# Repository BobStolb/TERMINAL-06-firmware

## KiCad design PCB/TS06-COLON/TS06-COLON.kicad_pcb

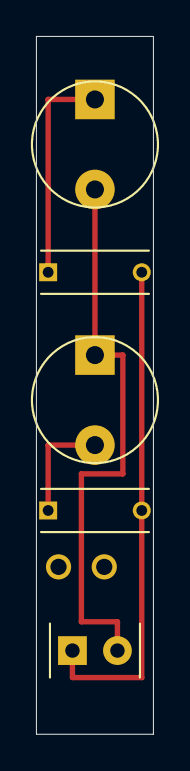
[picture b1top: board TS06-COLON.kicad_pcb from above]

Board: 2 copper layers, 6.5 x 38.8 mm, 5 parts (0 on the bottom side), 4 nets.

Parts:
R1, R2: 220k; TS06_R_Axial_EdgeToEdge
V1, V2: INS1; TS06_INS1_Lamp
XS4: XS4; TS06_XS4_JST_XH_2p_RA

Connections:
COLON_RET: V1.2, V2.1, XS4.2
HV185: R1.2, R2.2, XS4.1
R1_LINK: R1.1, V1.1
R2_LINK: R2.1, V2.2

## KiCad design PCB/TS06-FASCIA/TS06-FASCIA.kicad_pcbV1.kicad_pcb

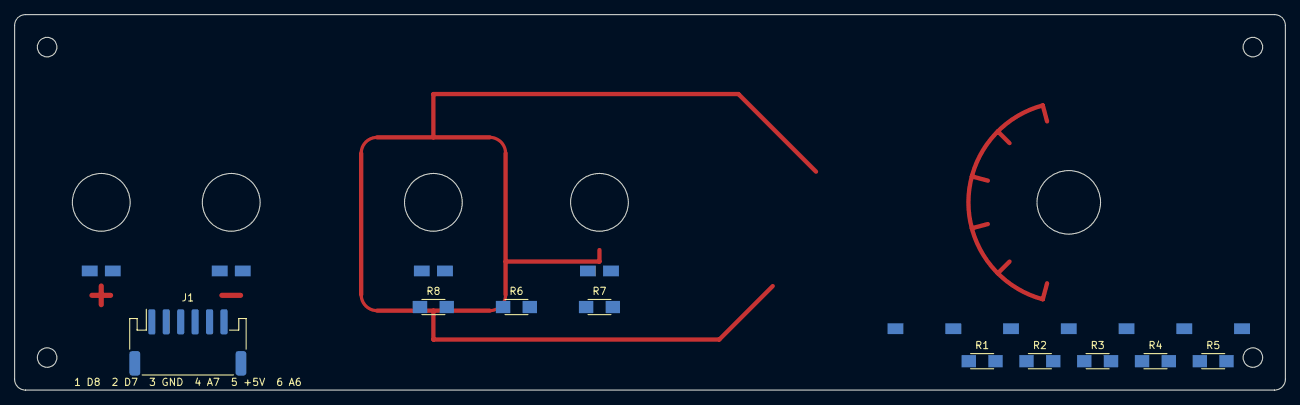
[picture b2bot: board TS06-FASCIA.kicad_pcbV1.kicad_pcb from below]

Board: 2 copper layers, 176.0 x 52.0 mm, 14 parts (9 on the bottom side), 12 nets, no tracks yet.

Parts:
J1: PH 6; TS06_JST_PH_S6B-PH-SM4-TB_Back
R1, R2, R3, R4, R5: 4k7; TS06_R_1206_HandSolder
R6, R8: 10k; TS06_R_1206_HandSolder
R7: 20k; TS06_R_1206_HandSolder
SW1: SR25 6-pos; TS06_Rotary_SR25_PanelMount
SW2: FIELD; TS06_MT1_Lever_PanelMount
SW3: SUB; TS06_MT1_Lever_PanelMount
SW4: MINUS; TS06_KMD1_Button_PanelMount
SW5: PLUS; TS06_KMD1_Button_PanelMount

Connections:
+5V: J1.5, R5.1, R6.1, SW1.6
A6: J1.6, SW1.7
A7: J1.4, R6.2, SW2.2, SW3.2
D7: J1.2, SW4.2
D8: J1.1, SW5.2
GND: J1.3, R1.2, R7.2, R8.2, SW1.1, SW4.1, SW5.1
LEVA: R7.1, SW2.1
LEVB: R8.1, SW3.1
TAP2: R1.1, R2.2, SW1.2
TAP3: R2.1, R3.2, SW1.3
TAP4: R3.1, R4.2, SW1.4
TAP5: R4.1, R5.2, SW1.5

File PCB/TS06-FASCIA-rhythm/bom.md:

# TS06-FASCIA-rhythm (fascia R) rev B: bill of materials

Hand-written from `tools/mkpcb_fascia_rhythm.py` (its `VALUE` and `FP` tables); there was no BOM for the fascia before. The pair's BOMs
(`PCB/TS06-DISP/bom.md`, `PCB/TS06-DRV/bom.md`) are generated by `tools/bom_pair.py`; this one is not. Board: 191.4 x 40 mm, 2.0 mm FR4,
black mask, white silk, ENIG (`fab/ORDER.md`). Every part is on the back, soldered by hand; no plated hole.

| Qty | Part | Refs | Footprint | Notes |
|---|---|---|---|---|
| 1 | **JST B6B-PH-SM4-TB**: PH 2.0 mm, 6 way, **top entry (upright)**, SMD, two retention tabs | J1 | `TS06_JST_PH_B6B-PH-SM4-TB_Back` | **Rev B (7 October 2026); rev A had the side-entry S6B-PH-SM4-TB.** The plug (PHR-6) stands straight off the back and the wires leave straight back. The tabs carry the load. Pin 1 = +5V at the right seen from the front. Header height 6.0 mm *inferred* (`PCB/TS06-FASCIA-rhythm/J1-UPRIGHT.md`) |
| 1 | SR25-style 6-position rotary (galette), panel mount, 12 detents of 30 degrees | SW1 | `TS06_Rotary_SR25_PanelMount_Rhythm` | MODE; bushing 8.62 mm in a 9.2 mm hole (opened 0.4 mm in the ordered zip); body 25.00 mm behind the panel |
| 2 | МТ1 toggle lever, panel mount | SW2, SW3 | `TS06_MT1_Lever_PanelMount` | FIELD, SUB; bushing 7.82 mm in an 8.4 mm hole (ordered zip) |
| 2 | КМД1-1 pushbutton, panel mount | SW4, SW5 | `TS06_KMD1_Button_PanelMount` | minus, plus; bushing 7.82 mm in an 8.4 mm hole (ordered zip) |
| 5 | 4k7, 1206 | R1-R5 | `TS06_R_1206_HandSolder` | the A6 ladder under the rotary's landing pads |
| 2 | 10k, 1206 | R6, R8 | `TS06_R_1206_HandSolder` | R6 the A7 pull-up; R8 the SUB lever's pull-down |
| 1 | 20k, 1206 | R7 | `TS06_R_1206_HandSolder` | the FIELD lever's pull-down |
| 4 | M2.5 screw, with the case's heat-set insert | H1-H4 | `MountingHole_2.7mm` | 2.7 mm holes at the corners; the screws are case hardware (`3d/case-pair`) |

The resistors' tolerance and power are not stated in the board file. The lead to TS06-DRV J1 (two PHR-6 housings and twelve SPH-002T-P0.5S
crimps, or a ready-made lead, 180-200 mm, pin 1 to pin 1) is on TS06-DRV's BOM; its fascia end plugs into the upright J1 above. The
controls are wired by hand from their lugs to the landing pads on the back (the product page's Wiring view shows them).

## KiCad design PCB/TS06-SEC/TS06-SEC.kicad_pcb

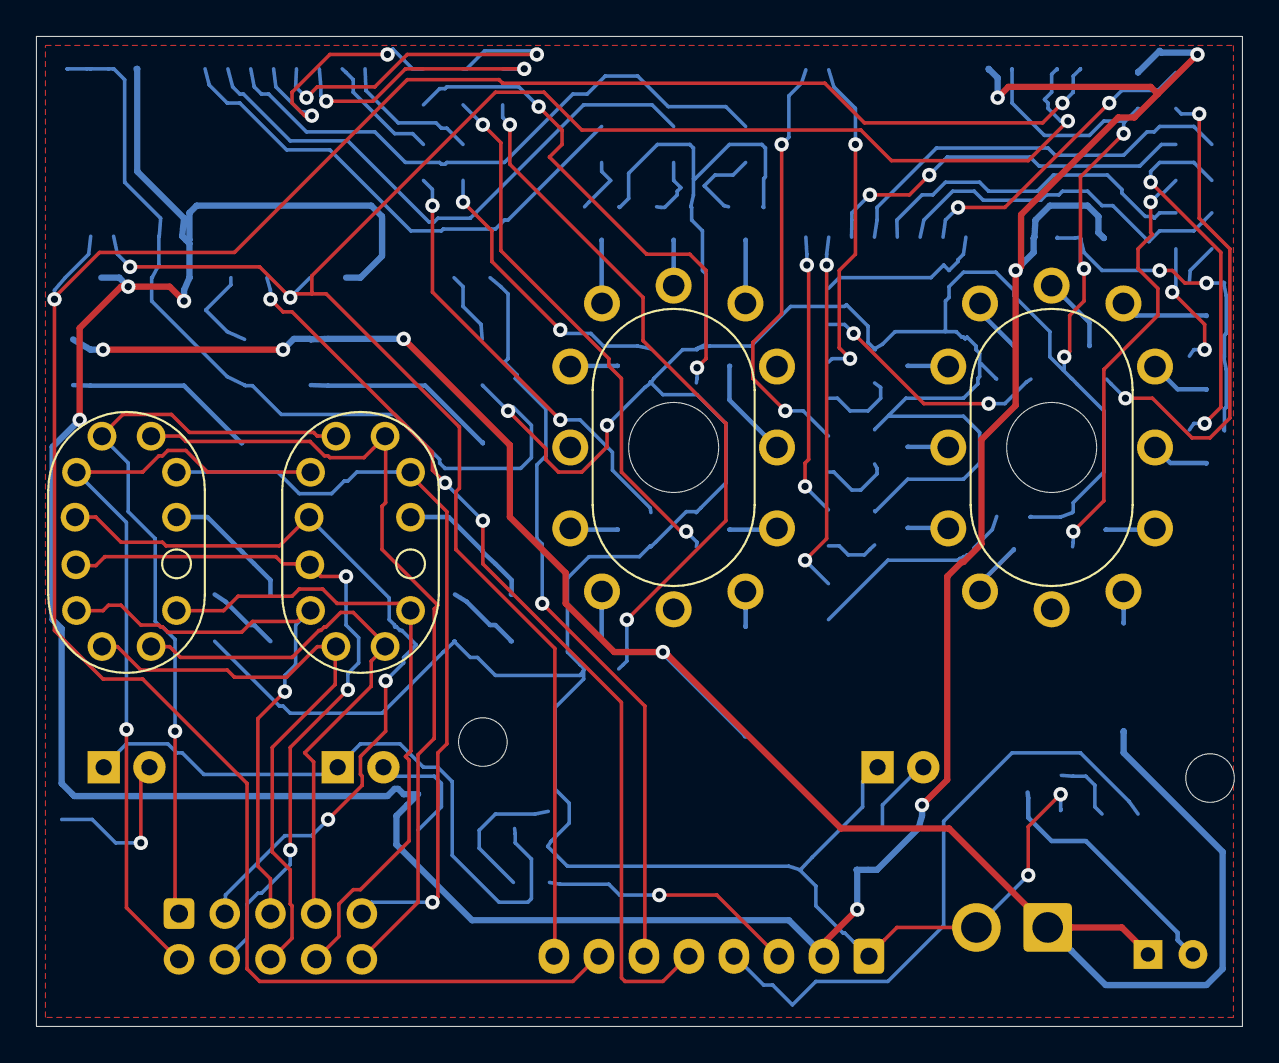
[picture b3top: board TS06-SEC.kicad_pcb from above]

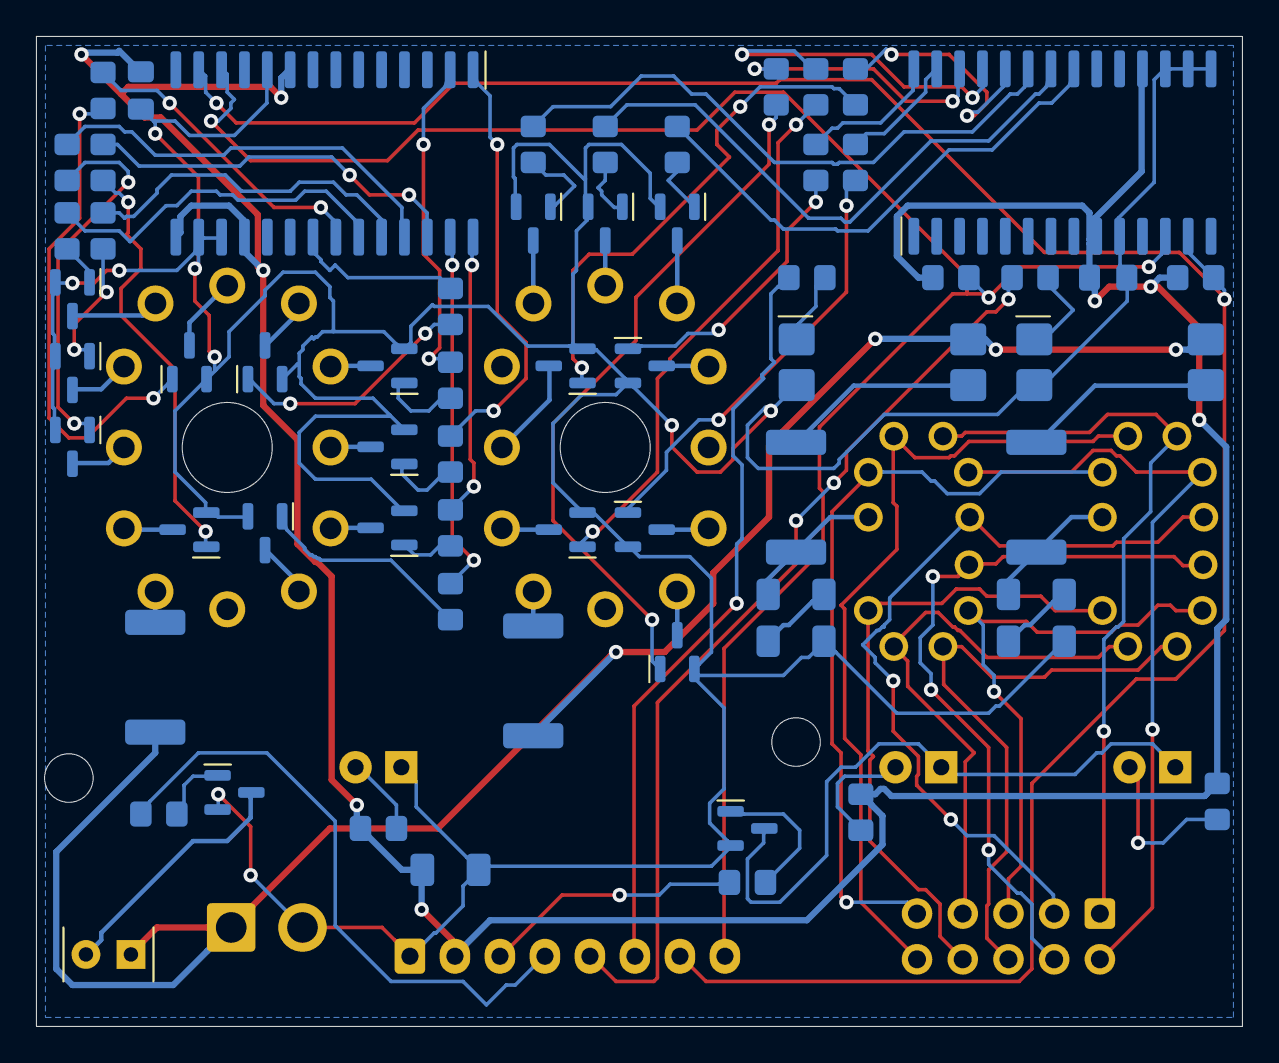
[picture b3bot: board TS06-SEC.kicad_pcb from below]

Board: 2 copper layers, 67.0 x 55.0 mm, 73 parts (66 on the bottom side), 90 nets.

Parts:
C1: 100n; TS06_C_0805_Back
C2: 100n; TS06_C_0805_Back_R90
C3: 10u; TS06_C_1206_Back
HL1, HL2, HL3: amber 3mm; TS06_LED_D3.0mm
R1: 10k; TS06_R_0805_Back
R2, R3, R4, R5, R6, R7, R8, R9, R10, R11, R12, R13, R14, R15, R16, R17, R18, R19: 10k; TS06_R_0805_Back_R90
R20: 1k; TS06_R_0805_Back
R21, R22: 100R; TS06_R_0805_Back
R23, R24: 12k; TS06_R_2512_Back_R90
R25, R27: 150R; TS06_R_0805_Back_R90
R26: 220R; TS06_R_0805_Back
R28, R29, R30, R31: 510k; TS06_R_1206_Back
R32, R33: 4k7 DNP; TS06_R_0805_Back
R38, R39: 8k2; TS06_R_2512_Back_R90
U3: MCP23017-E/SO; TS06_SOIC-28W_Back_R270
U4: MCP23017-E/SO; TS06_SOIC-28W_Back_R90
U5, U6: TLP627; TS06_SMDIP-4_Back
V5, V6: IN-17; TS06_IN17_Socket
V9: IN-15B; TS06_IN12_Socket
V10: IN-15A; TS06_IN12_Socket
VT1, VT8, VT9, VT20: MMBTA42; TS06_SOT-23_Std_Back
VT2, VT3, VT4, VT12, VT13, VT14, VT16: MMBTA42; TS06_SOT-23_Std_Back_R90
VT5, VT6, VT15, VT17, VT18, VT19: MMBTA42; TS06_SOT-23_Std_Back_R180
VT7, VT10, VT11: MMBTA42; TS06_SOT-23_Std_Back_R270
XS1: B2P-VH; TS06_JST_VH_B2P-VH_Back
XS2: IDC 2x5; TS06_IDC_2x05_Vertical_Back_R90
XS3: B8B-XH-A; TS06_JST_XH_B8B-XH-A_Back
XS4: B2B-XH-A; TS06_XS4_JST_XH_2p_RA

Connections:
+5V: C1.1, C2.1, C3.1, R25.1, R26.1, R27.1, R32.1, R33.1, U3.9, U3.18, U4.9, U4.15, U4.18, XS3.2
ANODE_AM: R38.1, V9.7
ANODE_PM: R39.1, V10.7
ANODE_S1: R24.2, R30.1, V6.A
ANODE_S10: R23.2, R28.1, V5.A
B1: R1.2, VT1.1
B2: R2.2, VT2.1
B3: R3.2, VT3.1
B4: R4.2, VT4.1
B5: R5.2, VT5.1
B6: R6.2, VT6.1
B7: R7.2, VT7.1
B8: R8.2, VT8.1
B9: R9.2, VT9.1
B10: R10.2, VT10.1
B11: R11.2, VT11.1
B12: R12.2, VT12.1
B13: R13.2, VT13.1
B14: R14.2, VT14.1
B15: R15.2, VT15.1
B16: R16.2, VT16.1
B17: R17.2, VT17.1
B18: R18.2, VT18.1
B19: R19.2, VT19.1
B20: R20.2, VT20.1
BACKL: R20.1, XS3.3
BLEED_S1: R30.2, R31.1
BLEED_S10: R28.2, R29.1
BL_A1: HL1.2, R25.2
BL_A2: HL2.2, R27.2
BL_K: HL1.1, HL2.1, VT20.3
CAT_A_KILO: V10.12, VT19.3
CAT_A_MEGA: V10.1, VT10.3
CAT_A_MICRO: V10.6, VT15.3
CAT_A_MILLI: V10.2, VT11.3
CAT_A_MINUS: V10.4, VT13.3
CAT_A_NANO: V10.9, VT16.3
CAT_A_P: V10.5, VT14.3
CAT_A_PCT: V10.10, VT17.3
CAT_A_PI: V10.11, VT18.3
CAT_A_PLUS: V10.3, VT12.3
CAT_B_AMP: V9.9, VT7.3
CAT_B_FARAD: V9.5, VT5.3
CAT_B_HENRY: V9.2, VT3.3
CAT_B_HERTZ: V9.3, VT4.3
CAT_B_OHM: V9.10, VT8.3
CAT_B_SIEMENS: V9.12, VT9.3
CAT_B_VOLT: V9.1, VT2.3
CAT_B_WATT: V9.6, VT6.3
COLON_RET: VT1.3, XS4.2
DOT: R1.1, XS3.4
EMIT_S1: R24.1, U6.3
EMIT_S10: R23.1, U5.3
GND: C1.2, C2.2, C3.2, HL3.1, R29.2, R31.2, U3.10, U3.15, U3.16, U3.17, U4.10, U4.16, U4.17, U5.2, U6.2, VT1.2, VT2.2, VT3.2, VT4.2, VT5.2, VT6.2, VT7.2, VT8.2, VT9.2, VT10.2, VT11.2, VT12.2, VT13.2, VT14.2, VT15.2, VT16.2, VT17.2, VT18.2, VT19.2, VT20.2, XS1.2, XS3.1
HV185: R38.2, R39.2, U5.4, U6.4, XS1.1, XS4.1
K0: V5.0, V6.0, XS2.9
K1: V5.1, V6.1, XS2.10
K2: V5.2, V6.2, XS2.1
K3: V5.3, V6.3, XS2.2
K4: V5.4, V6.4, XS2.3
K5: V5.5, V6.5, XS2.4
K6: V5.6, V6.6, XS2.5
K7: V5.7, V6.7, XS2.6
K8: V5.8, V6.8, XS2.7
K9: V5.9, V6.9, XS2.8
LED_A0: R21.2, U5.1
LED_A1: R22.2, U6.1
M_A: HL3.2, R26.2
SCL: R33.2, U3.12, U4.12, XS3.8
SDA: R32.2, U3.13, U4.13, XS3.7
SEC_A0: R21.1, XS3.5
SEC_A1: R22.1, XS3.6
U3_GPA0: R2.1, U3.21
U3_GPA1: R3.1, U3.22
U3_GPA2: R4.1, U3.23
U3_GPA3: R5.1, U3.24
U3_GPA4: R6.1, U3.25
U3_GPA5: R7.1, U3.26
U3_GPA6: R8.1, U3.27
U3_GPA7: R9.1, U3.28
U4_GPA0: R10.1, U4.21
U4_GPA1: R11.1, U4.22
U4_GPA2: R12.1, U4.23
U4_GPA3: R13.1, U4.24
U4_GPA4: R14.1, U4.25
U4_GPA5: R15.1, U4.26
U4_GPA6: R16.1, U4.27
U4_GPA7: R17.1, U4.28
U4_GPB0: R18.1, U4.1
U4_GPB1: R19.1, U4.2
